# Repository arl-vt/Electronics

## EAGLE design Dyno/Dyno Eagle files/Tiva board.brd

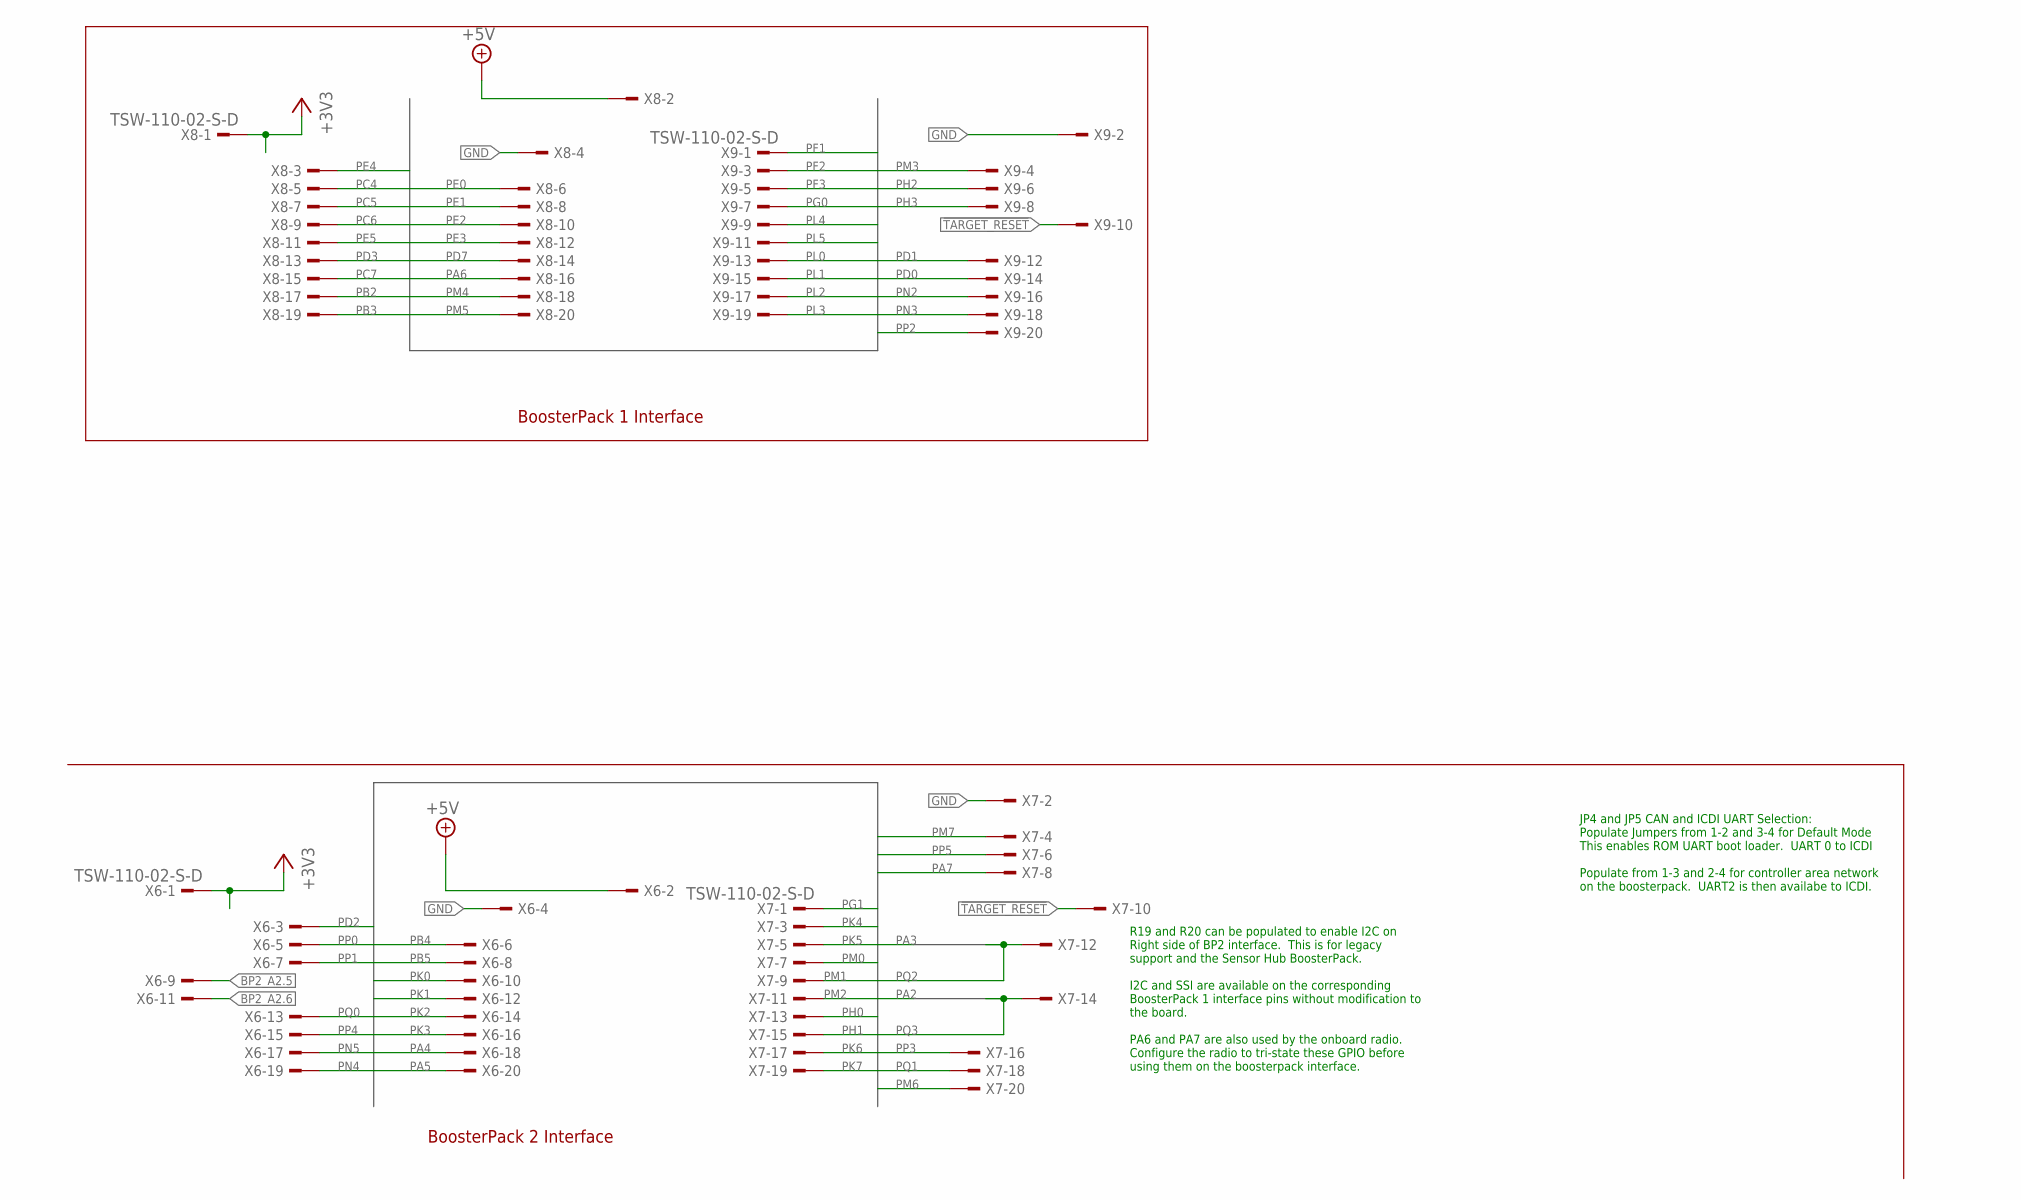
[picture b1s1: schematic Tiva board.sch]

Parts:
X6, X7, X8, X9: TSW-110-02-S-D

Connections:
!TARGET_RESET: X7.10, X9.10
+3V3: X6.1, X8.1
+5V: X6.2, X8.2
BP2_A2.5: X6.9
BP2_A2.6: X6.11
GND: X6.4, X7.2, X8.4, X9.2
PA4: X6.18
PA5: X6.20
PA6: X8.16
PA7: X7.8
PB2: X8.17
PB3: X8.19
PB4: X6.6
PB5: X6.8
PC4: X8.5
PC5: X8.7
PC6: X8.9
PC7: X8.15
PD0: X9.14
PD1: X9.12
PD2: X6.3
PD3: X8.13
PD7: X8.14
PE0: X8.6
PE1: X8.8
PE2: X8.10
PE3: X8.12
PE4: X8.3
PE5: X8.11
PF1: X9.1
PF2: X9.3
PF3: X9.5
PG0: X9.7
PG1: X7.1
PH0: X7.13
PH1: X7.15
PH2: X9.6
PH3: X9.8
PK0: X6.10
PK1: X6.12
PK2: X6.14
PK3: X6.16
PK4: X7.3
PK5: X7.5
PK6: X7.17
PK7: X7.19
PL0: X9.13
PL1: X9.15
PL2: X9.17
PL3: X9.19
PL4: X9.9
PL5: X9.11
PM0: X7.7
PM1: X7.9
PM2: X7.11
PM3: X9.4
PM4: X8.18
PM5: X8.20
PM6: X7.20
PM7: X7.4
PN2: X9.16
PN3: X9.18
PN4: X6.19
PN5: X6.17
PP0: X6.5
PP1: X6.7
PP2: X9.20
PP3: X7.16
PP4: X6.15
PP5: X7.6
PQ0: X6.13
PQ1: X7.18
PQ2: X7.12
PQ3: X7.14

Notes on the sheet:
BoosterPack 2 Interface
BoosterPack 1 Interface
JP4 and JP5 CAN and ICDI UART Selection: Populate Jumpers from 1-2 and 3-4 for Default Mode This enables ROM UART boot loader. UART 0 to ICDI Populate from 1-3 and 2-4 for controller area network on the boosterpack. UART2 is then availabe to ICDI.
R19 and R20 can be populated to enable I2C on Right side of BP2 interface. This is for legacy support and the Sensor Hub BoosterPack. I2C and SSI are available on the corresponding BoosterPack 1 interface pins without modification to the board. PA6 and PA7 are also used by the onboard radio. Config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

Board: 2 copper layers, 4 parts (0 on the bottom side), 4 nets, no tracks yet.

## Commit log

2016-09-09 Added getting strated codes
2016-09-21 inital files for development of dyno test stand. Eagle cad files and CCS Tiva Code
2016-09-26 Timer and Interrput getting started
2016-10-19 PWM and Timers and interrupts
2016-10-26 UART example added
2016-10-26 ADC Codes added
2016-11-10 TM4c129 Launch Pad tutorials
2016-12-21 add all changes
2016-12-21 Added DC Motor
    DC Motor with Advanced Motion AZBDC12A8 servo driver and TM4C123
2017-05-19 PWM ,motor
